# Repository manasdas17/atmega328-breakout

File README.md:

# ATMEGA328 Breakout Board
Simple breakout board for an ATMEGA328.

Untested as of yet.

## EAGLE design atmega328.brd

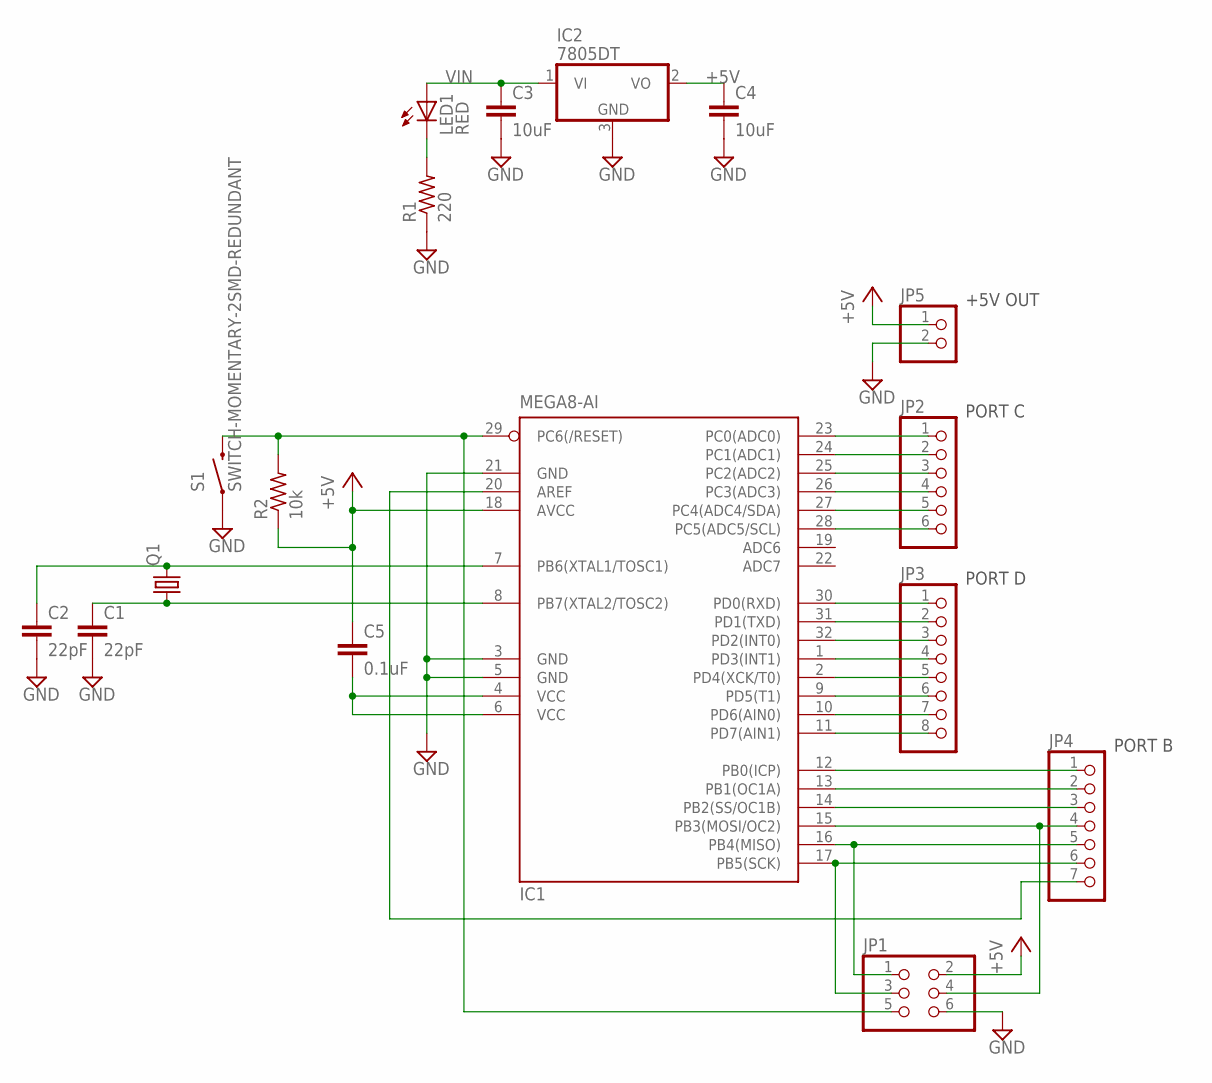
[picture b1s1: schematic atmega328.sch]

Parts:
C1, C2: 22pF; C0805
C3, C4: 10uF; C0805
C5: 0.1uF; C0805
IC1: MEGA8-AI; TQFP32-08
IC2: 7805DT; TO252
JP1: PINHD-2X3; 2X03
JP2: PINHD-1X6; 1X06
JP3: PINHD-1X8; 1X08
JP4: PINHD-1X7; 1X07
JP5: PINHD-1X2; 1X02
LED1: RED; CHIPLED_0805
Q1: CRYSTALHC49UP; HC49UP
R1: 220; R0805
R2: 10k; R0805
S1: SWITCH-MOMENTARY-2SMD-REDUNDANT; TACTILE-SWITCH-SMD

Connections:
+5V: C4.1, C5.1, IC1.18 (AVCC), IC2.2 (VO), JP1.2, JP5.1, R2.1
GND: C1.2, C2.2, C3.2, C4.2, IC1.3 (GND), IC1.5 (GND), IC1.21 (GND), IC2.3 (GND), JP1.6, JP5.2, R1.1, S1.1, S1.2 (1)
unnamed: C2.1, IC1.7 (PB6(XTAL1/TOSC1)), Q1.2
unnamed: LED1.C, R1.2
unnamed: C1.1, IC1.8 (PB7(XTAL2/TOSC2)), Q1.1
unnamed: IC1.29 (PC6(/RESET)), JP1.5, R2.2, S1.3 (2), S1.4 (2)
unnamed: IC1.23 (PC0(ADC0)), JP2.1
unnamed: IC1.24 (PC1(ADC1)), JP2.2
unnamed: IC1.25 (PC2(ADC2)), JP2.3
unnamed: IC1.26 (PC3(ADC3)), JP2.4
unnamed: IC1.27 (PC4(ADC4/SDA)), JP2.5
unnamed: IC1.28 (PC5(ADC5/SCL)), JP2.6
unnamed: IC1.30 (PD0(RXD)), JP3.1
unnamed: IC1.31 (PD1(TXD)), JP3.2
unnamed: IC1.32 (PD2(INT0)), JP3.3
unnamed: IC1.1 (PD3(INT1)), JP3.4
unnamed: IC1.2 (PD4(XCK/T0)), JP3.5
unnamed: IC1.9 (PD5(T1)), JP3.6
unnamed: IC1.10 (PD6(AIN0)), JP3.7
unnamed: IC1.11 (PD7(AIN1)), JP3.8
unnamed: IC1.12 (PB0(ICP)), JP4.1
unnamed: IC1.13 (PB1(OC1A)), JP4.2
unnamed: IC1.14 (PB2(SS/OC1B)), JP4.3
unnamed: IC1.15 (PB3(MOSI/OC2)), JP1.4, JP4.4
unnamed: IC1.16 (PB4(MISO)), JP1.1, JP4.5
unnamed: IC1.17 (PB5(SCK)), JP1.3, JP4.6
unnamed: IC1.20 (AREF), JP4.7
unnamed: C5.2, IC1.4 (VCC), IC1.6 (VCC)
VIN: C3.1, IC2.1 (VI), LED1.A

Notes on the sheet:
PORT C
PORT D
PORT B
+5V OUT

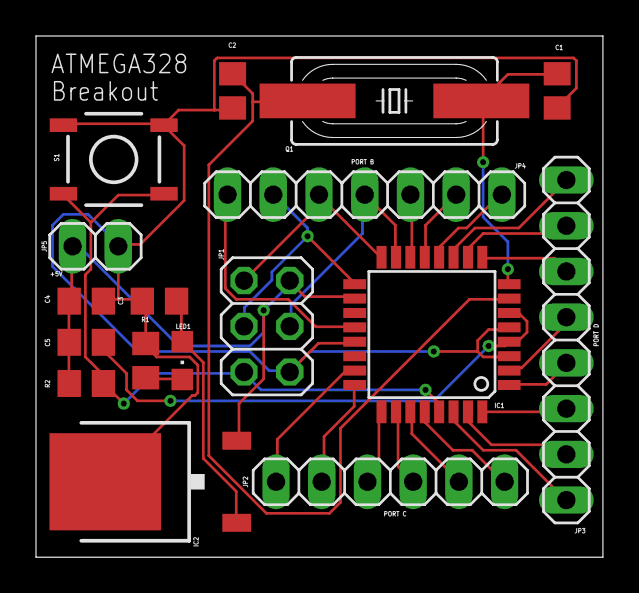
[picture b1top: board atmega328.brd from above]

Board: 2 copper layers, 31.5 x 29.0 mm, 17 parts (0 on the bottom side), 29 nets.

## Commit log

2015-08-29 Remove eagle.epf
    Unnecessary file to track

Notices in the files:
parts and their libraries:
SparkFun-Electromechanical: Licensing: Creative Commons ShareAlike 4.0 International - https://creativecommons.org/licenses/by-sa/4.0
